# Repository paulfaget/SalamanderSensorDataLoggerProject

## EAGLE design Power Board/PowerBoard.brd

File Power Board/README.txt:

Salamander Project
BatBoard information

This portion of the salamander project is a daughter card that is intended to mate to the Moteiv tmote sky radio module. It acts as a voltage controller to provide 3v to the radio and 5v to the sensors and also provide level translation for connected sensors.

Input voltage range:5.38V-16V
Power switch on when switched AWAY from battery connector.

Pinouts: 
SV1:Pin 2 - GIO3 interface to Mote
SV2:Pin 2 - UART0 TX interface to Mote (SEE NOTE 1!)
SV2:Pin 6 - 3V power to Mote
SV2:Pin 10 - GND 
X1: P - 5V power to sensor board
X1: D - 5V level-translated 1-wire
X1: G - GND to sensor board

Resistor Positions:
R2: Populate to level-translate 3V logic UART TX to 5V on X1-D
P3: Populate to level-translate 1-wire from 5V to 3V
****DO NOT POPULATE BOTH RESISTORS SIMULTANEOUSLY!****

NOTE 1:
As the project currently stands, UART0 is not enabled on the radio board. The ability to choose between interfacing this board between 1-wire and the UART allows a radio to be assigned as a "listener," and to connect to loggers that can only accept 5V logic. This is accomplished by populating the R2 *OR* R3 positions with a 0 Ohm resistor as described above. With the firmware currently on the radios, UART0 is not enabled: the UART1 output must be tapped from the FTDI serial->USB chip, and jumpered to the left position of the R2 solder pad and neither R2 or R3 should be populated.

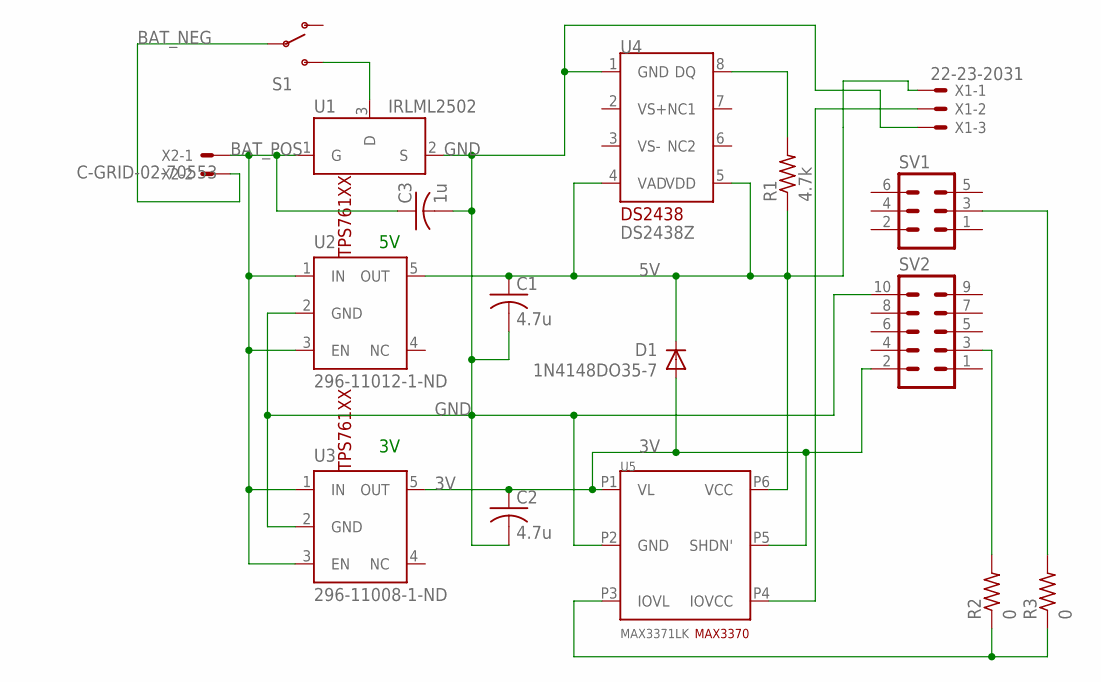
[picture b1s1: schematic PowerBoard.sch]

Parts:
C1, C2: 4.7u; C0805
C3: 1u; C0805
D1: 1N4148DO35-7; DO35-7
R1: 4.7k; M0805
R2, R3: 0; R0805
S1: SWITCH-SPST-SMD-A
SV1: MA03-2
SV2: MA05-2
U1: IRLML2502; SOT23
U2: 296-11012-1-ND; SOT23-DBV
U3: 296-11008-1-ND; SOT23-DBV
U4: DS2438Z; SOIC08
U5: MAX3371LK; 6-LEAD-SC70
X1: 22-23-2031
X2: C-GRID-02-70553; 70553-02

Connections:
3V: C2.1, D1.A, SV2.2, U3.5 (OUT), U5.P1 (VL), U5.P5 (SHDN')
5V: C1.1, D1.C, R1.1, U2.5 (OUT), U4.4 (VAD), U4.5 (VDD), U5.P6 (VCC), X1.1
BAT_NEG: S1.2, X2.2
BAT_POS: C3.1, U1.1 (G), U2.1 (IN), U2.3 (EN), U3.1 (IN), U3.3 (EN), X2.1
GND: C1.2, C2.2, C3.2, SV2.10, U1.2 (S), U2.2 (GND), U3.2 (GND), U4.1 (GND), U5.P2 (GND), X1.3
unnamed: R2.1, R3.1, U5.P3 (IOVL)
unnamed: S1.3 (S), U1.3 (D)
unnamed: R1.2, U4.8 (DQ)
unnamed: U5.P4 (IOVCC), X1.2
unnamed: R3.2, SV1.3
unnamed: R2.2, SV2.3

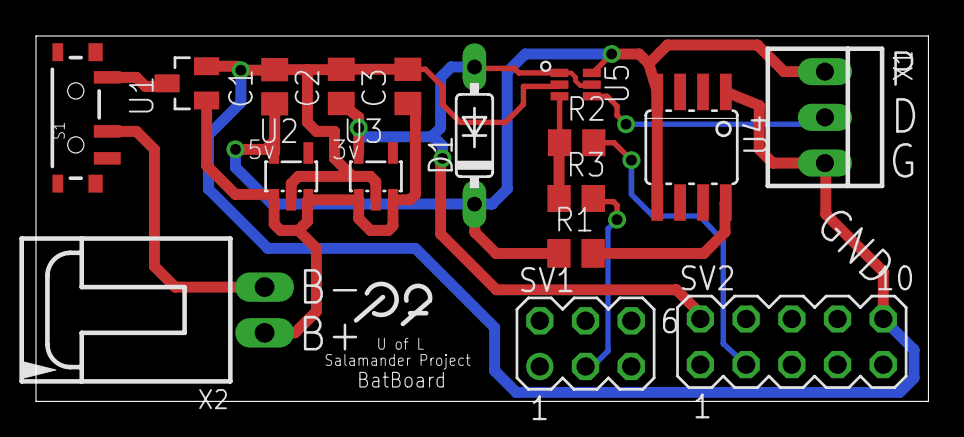
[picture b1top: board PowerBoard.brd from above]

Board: 2 copper layers, 49.6 x 20.3 mm, 17 parts (0 on the bottom side), 11 nets.

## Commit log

2012-07-11 Initial commit
    This was the version of the Power Board that was sent out for
    production. It came back with a successful, functional, build.
2012-07-14 Two files added
    Added a colorized and enlarged PDF of the board as well as a README
    describing its functionality.
2012-07-20 Project "wrapup"
    Added images of enclosure, README to explain connections and layout, and
    Wrapup.txt explaining where the project still needs to be taken.

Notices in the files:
parts and their libraries:
SparkFun: Licensing: CC v3.0 Share-Alike You are welcome to use this library for commercial purposes.
